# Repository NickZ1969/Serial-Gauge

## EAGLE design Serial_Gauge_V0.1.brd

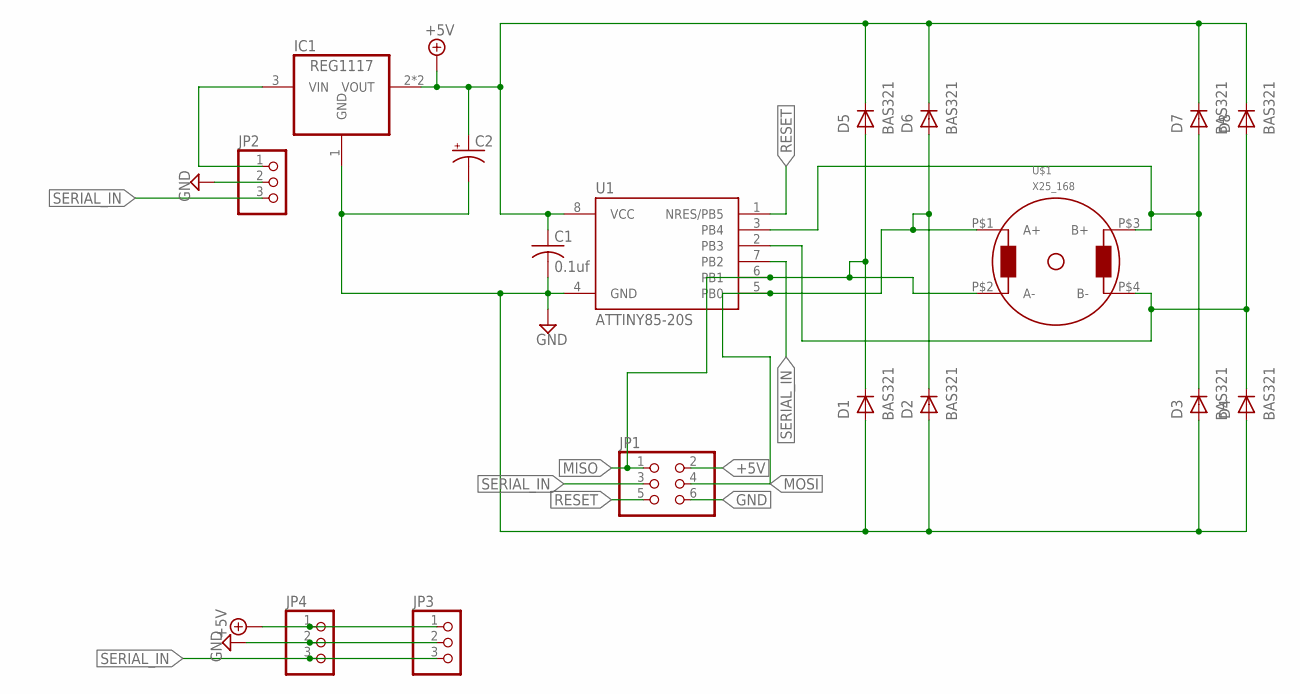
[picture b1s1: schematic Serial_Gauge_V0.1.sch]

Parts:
C1: 0.1uf; C1206K
C2: CPOL-US140CLH-0810; 140CLH-0810
D1, D2, D3, D4, D5, D6, D7, D8: BAS321; SOD323(F)
IC1: REG1117; SOT223
JP1: PINHD-2X3; 2X03
JP2, JP3, JP4: PINHD-1X3; 1X03
U1: ATTINY85-20S; SOIC8_EIAJ_208MIL
U$1: X25_168

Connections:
+5V: C1.1, C2.+, D5.1 (K), D6.1 (K), D7.1 (K), D8.1 (K), IC1.2 (VOUT), IC1.4 (VOUT), JP1.2, JP3.1, JP4.1, U1.8 (VCC)
GND: C1.2, C2.-, D1.2 (A), D2.2 (A), D3.2 (A), D4.2 (A), IC1.1 (GND), JP1.6, JP2.2, JP3.2, JP4.2, U1.4 (GND)
MISO: D1.1 (K), D5.2 (A), JP1.1, U1.6 (PB1), U$1.P$2 (A-)
MOSI: D2.1 (K), D6.2 (A), JP1.4, U1.5 (PB0), U$1.P$1 (A+)
unnamed: IC1.3 (VIN), JP2.1
unnamed: D4.1 (K), D8.2 (A), U1.2 (PB3), U$1.P$4 (B-)
unnamed: D3.1 (K), D7.2 (A), U1.3 (PB4), U$1.P$3 (B+)
RESET: JP1.5, U1.1 (NRES/PB5)
SERIAL_IN: JP1.3, JP2.3, JP3.3, JP4.3, U1.7 (PB2)

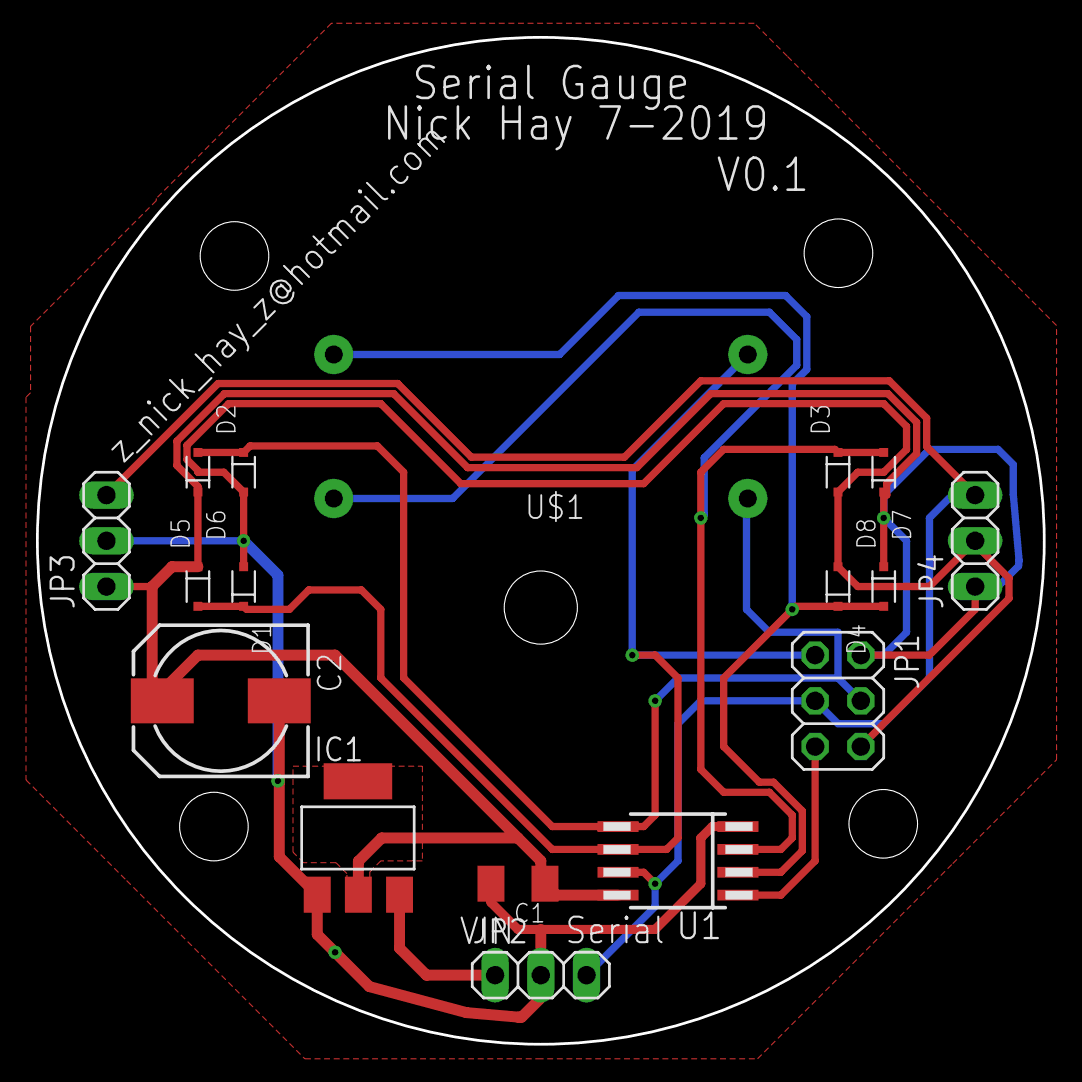
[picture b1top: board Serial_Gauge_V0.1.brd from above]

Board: 2 copper layers, 55.9 x 55.9 mm, 17 parts (0 on the bottom side), 9 nets.

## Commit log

2019-08-25 Arduino code for serial gauge.
2019-08-25 Eagle cad files for serial gauge
